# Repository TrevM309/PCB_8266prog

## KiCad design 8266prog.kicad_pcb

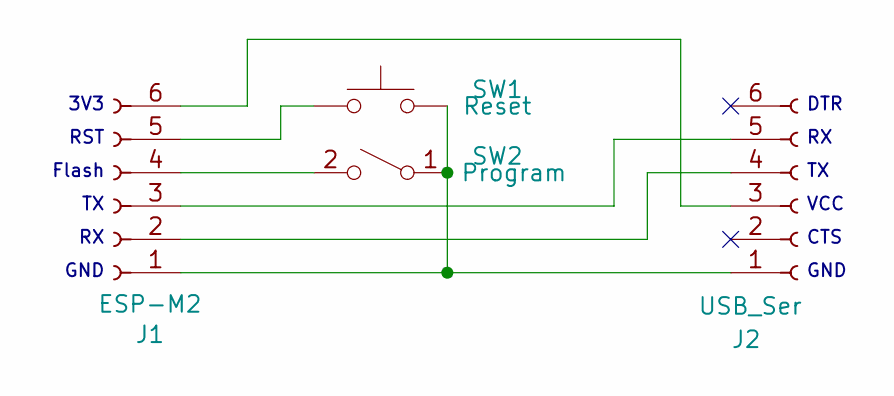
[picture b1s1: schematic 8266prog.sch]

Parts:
J1: ESP-M2; PinSocket_1x06_P2.54mm_Horizontal
J2: USB_Ser; PinSocket_1x06_P2.54mm_Horizontal
SW1: Reset; SW_SPST_PTS645
SW2: Program; SlideSwitch

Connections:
unnamed: J1.1, J2.1, SW1.2, SW2.1 (A)
unnamed: J1.2, J2.4
unnamed: J1.3, J2.5
unnamed: J1.4, SW2.2 (B)
unnamed: J1.5, SW1.1
unnamed: J1.6, J2.3

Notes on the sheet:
DTR
VCC
CTS
GND
3V3
RST
Flash

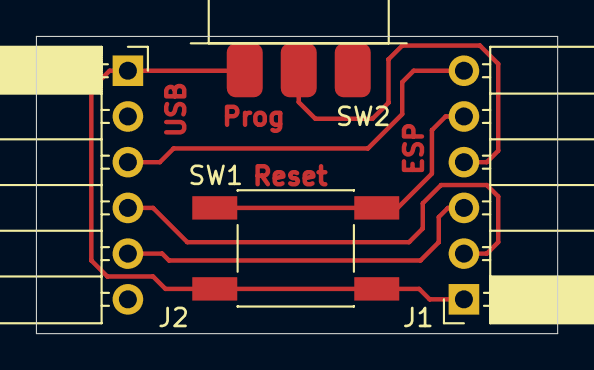
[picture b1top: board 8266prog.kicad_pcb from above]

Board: 2 copper layers, 29.0 x 16.5 mm, 4 parts (0 on the bottom side), 6 nets.

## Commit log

2021-05-12 Good, PCB ok, added text to show connectors after etch
2021-05-14 was a Balls up, re-do
2021-05-14 Minor tweaks, then created, works ok
2021-08-08 add README.md
